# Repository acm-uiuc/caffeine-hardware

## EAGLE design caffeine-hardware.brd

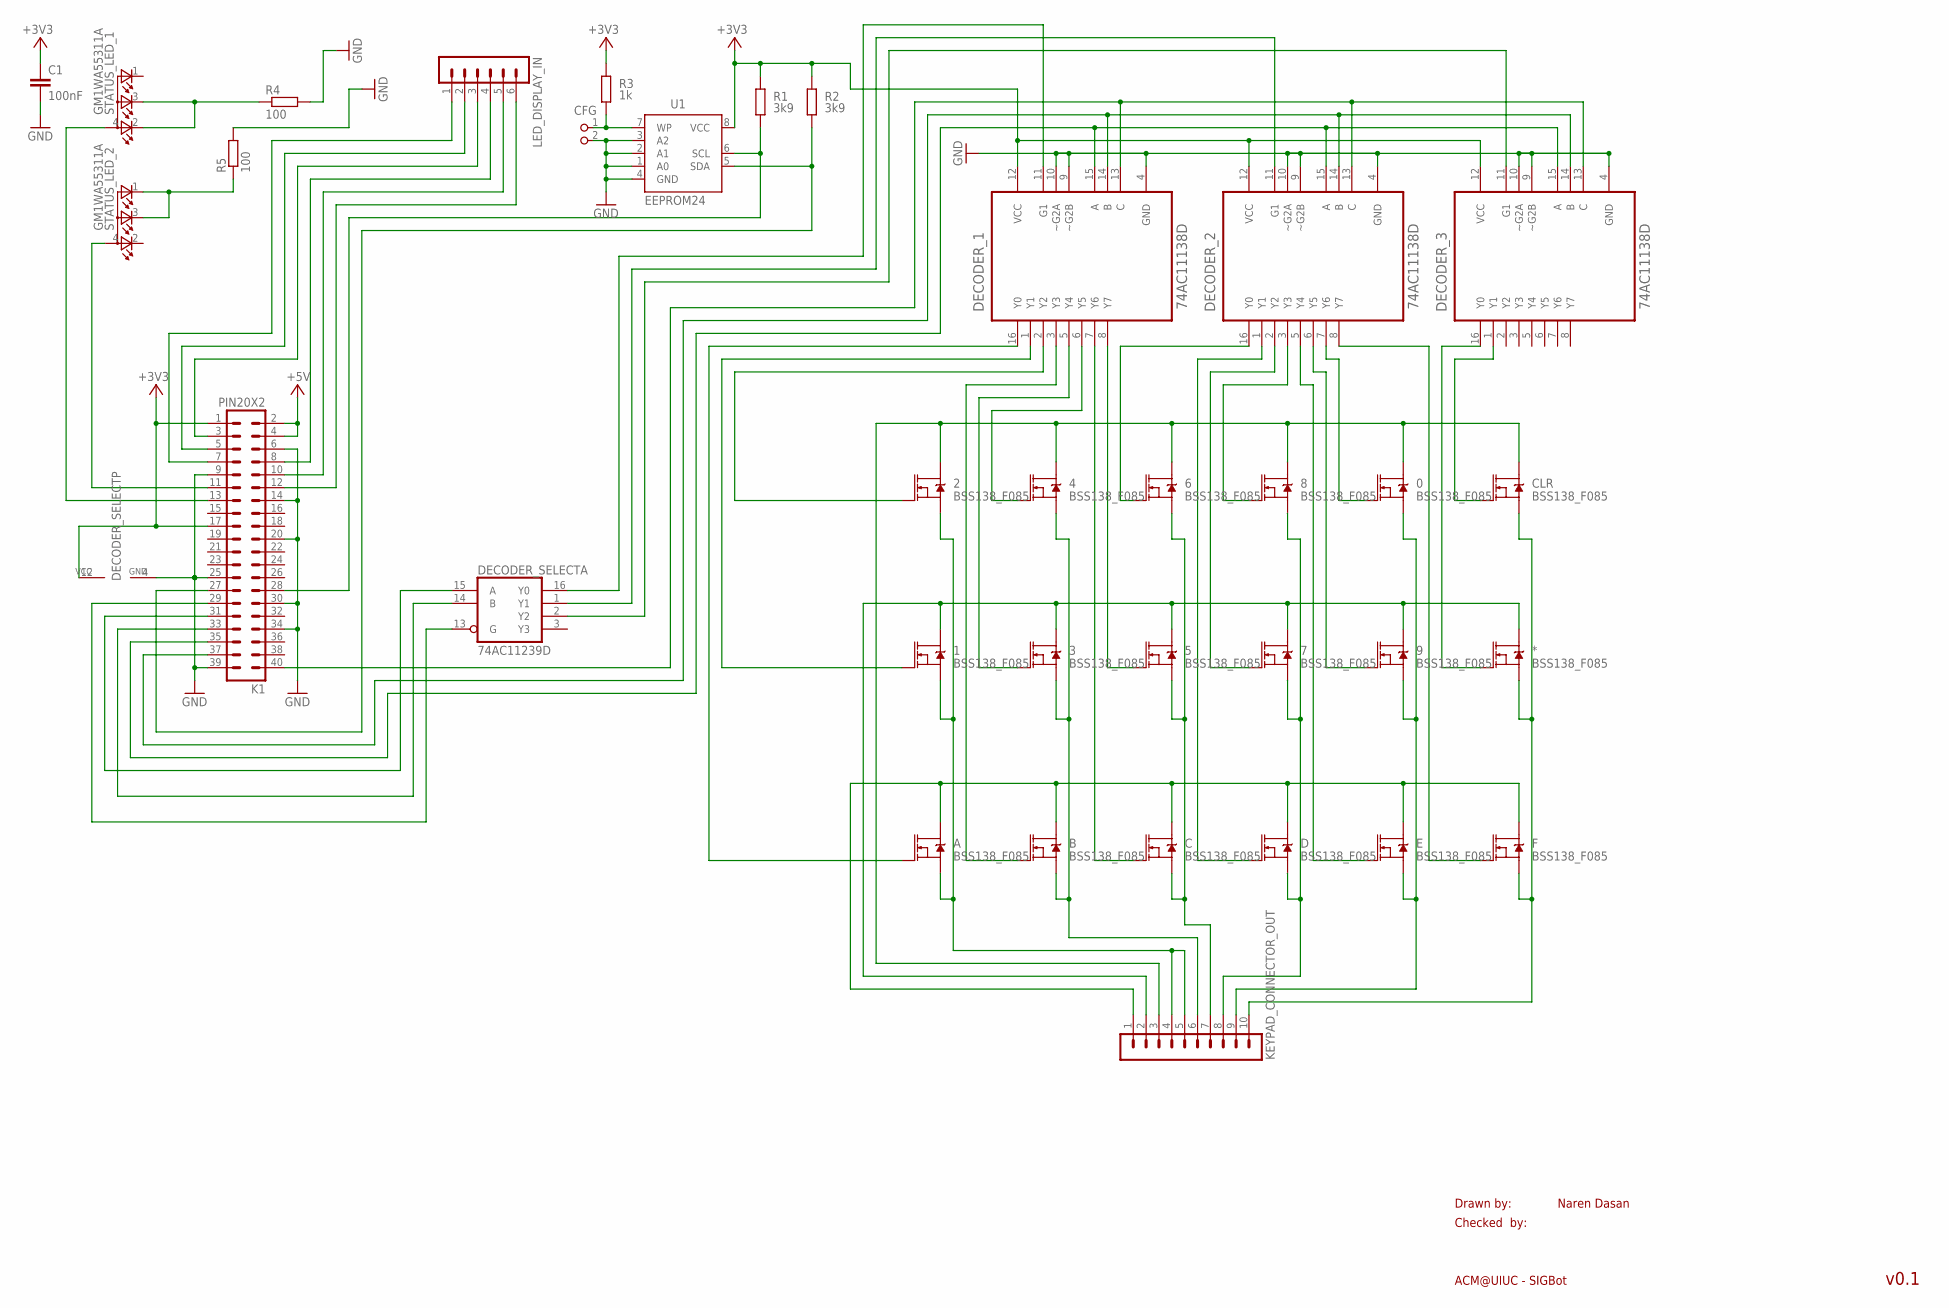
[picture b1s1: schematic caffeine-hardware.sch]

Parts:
0, 1, 2, 3, 4, 5, 6, 7, 8, 9: BSS138_F085; SOT23-3
*: BSS138_F085; SOT23-3
A: BSS138_F085; SOT23-3
B: BSS138_F085; SOT23-3
C: BSS138_F085; SOT23-3
C1: 100nF; C0805K
CFG: PIN2_100; PIN_W_2
CLR: BSS138_F085; SOT23-3
D: BSS138_F085; SOT23-3
DECODER_1, DECODER_2, DECODER_3: 74AC11138D; SOIC127P600X175-16N
DECODER_SELECT: 74AC11239D; SO16
E: BSS138_F085; SOT23-3
F: BSS138_F085; SOT23-3
K1: PIN20X2; PIN_20X2
KEYPAD_CONNECTOR_OUT: MA10-1
LED_DISPLAY_IN: MA06-1
R1, R2: 3k9; M0805; TOLERANCE 5%
R3: 1k; M0805; TOLERANCE 5%
R4, R5: 100; R0805
STATUS_LED_1, STATUS_LED_2: GM1WA55311A
U1: EEPROM24; SOIC8

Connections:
+3V3: C1.1, DECODER_1.12 (VCC), DECODER_2.12 (VCC), DECODER_3.12 (VCC), DECODER_SELECT.12 (VCC), K1.1, K1.17, R1.2, R2.2, R3.2, U1.8 (VCC)
+5V: K1.2, K1.4
GND: C1.2, CFG.2, DECODER_1.4 (GND), DECODER_1.9 (~G2B), DECODER_1.10 (~G2A), DECODER_2.4 (GND), DECODER_2.9 (~G2B), DECODER_2.10 (~G2A), DECODER_3.4 (GND), DECODER_3.9 (~G2B), DECODER_3.10 (~G2A), DECODER_SELECT.4 (GND), K1.6, K1.9, K1.14, K1.20, K1.25, K1.30, K1.34, K1.39, R4.2, R5.2, U1.1 (A0), U1.2 (A1), U1.3 (A2), U1.4 (GND)
unnamed: K1.28, R1.1, U1.6 (SCL)
unnamed: K1.27, R2.1, U1.5 (SDA)
unnamed: CFG.1, R3.1, U1.7 (WP)
unnamed: A.3 (D), B.3 (D), C.3 (D), D.3 (D), E.3 (D), F.3 (D), KEYPAD_CONNECTOR_OUT.1
unnamed: 1.3 (D), 3.3 (D), 5.3 (D), 7.3 (D), 9.3 (D), *.3 (D), KEYPAD_CONNECTOR_OUT.2
unnamed: 0.3 (D), 2.3 (D), 4.3 (D), 6.3 (D), 8.3 (D), CLR.3 (D), KEYPAD_CONNECTOR_OUT.3
unnamed: 5.2 (S), 6.2 (S), C.2 (S), KEYPAD_CONNECTOR_OUT.7
unnamed: 7.2 (S), 8.2 (S), D.2 (S), KEYPAD_CONNECTOR_OUT.8
unnamed: 1.2 (S), 2.2 (S), A.2 (S), KEYPAD_CONNECTOR_OUT.4, KEYPAD_CONNECTOR_OUT.5
unnamed: DECODER_1.11 (G1), DECODER_SELECT.16 (Y0)
unnamed: 0.2 (S), 9.2 (S), E.2 (S), KEYPAD_CONNECTOR_OUT.9
unnamed: *.2 (S), CLR.2 (S), F.2 (S), KEYPAD_CONNECTOR_OUT.10
unnamed: 3.2 (S), 4.2 (S), B.2 (S), KEYPAD_CONNECTOR_OUT.6
unnamed: DECODER_SELECT.14 (B), K1.33
unnamed: DECODER_1.15 (A), DECODER_2.15 (A), DECODER_3.15 (A), K1.35
unnamed: DECODER_1.14 (B), DECODER_2.14 (B), DECODER_3.14 (B), K1.37
unnamed: DECODER_1.13 (C), DECODER_2.13 (C), DECODER_3.13 (C), K1.40
unnamed: DECODER_SELECT.15 (A), K1.31
unnamed: DECODER_2.11 (G1), DECODER_SELECT.1 (Y1)
unnamed: DECODER_3.11 (G1), DECODER_SELECT.2 (Y2)
unnamed: DECODER_SELECT.13 (G), K1.29
unnamed: A.1 (G), DECODER_1.16 (Y0)
unnamed: 1.1 (G), DECODER_1.1 (Y1)
unnamed: 2.1 (G), DECODER_1.2 (Y2)
unnamed: B.1 (G), DECODER_1.3 (Y3)
unnamed: 3.1 (G), DECODER_1.5 (Y4)
unnamed: 4.1 (G), DECODER_1.6 (Y5)
unnamed: C.1 (G), DECODER_1.7 (Y6)
unnamed: 5.1 (G), DECODER_1.8 (Y7)
unnamed: K1.7, LED_DISPLAY_IN.1
unnamed: K1.5, LED_DISPLAY_IN.2
unnamed: K1.8, LED_DISPLAY_IN.4
unnamed: K1.3, LED_DISPLAY_IN.3
unnamed: K1.12, LED_DISPLAY_IN.6
unnamed: K1.10, LED_DISPLAY_IN.5
unnamed: K1.11, STATUS_LED_2.4 (A)
unnamed: K1.13, STATUS_LED_1.4 (A)
unnamed: R4.1, STATUS_LED_1.2 (CRED), STATUS_LED_1.3 (CBLUE)
unnamed: R5.1, STATUS_LED_2.1 (CGREEN), STATUS_LED_2.3 (CBLUE)
unnamed: 6.1 (G), DECODER_2.16 (Y0)
unnamed: D.1 (G), DECODER_2.1 (Y1)
unnamed: 7.1 (G), DECODER_2.2 (Y2)
unnamed: 8.1 (G), DECODER_2.3 (Y3)
unnamed: DECODER_2.5 (Y4), E.1 (G)
unnamed: 9.1 (G), DECODER_2.6 (Y5)
unnamed: 0.1 (G), DECODER_2.7 (Y6)
unnamed: DECODER_2.8 (Y7), F.1 (G)
unnamed: *.1 (G), DECODER_3.16 (Y0)
unnamed: CLR.1 (G), DECODER_3.1 (Y1)

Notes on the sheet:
Drawn by:
Checked by:
ACM@UIUC - SIGBot
Naren Dasan
v0.1

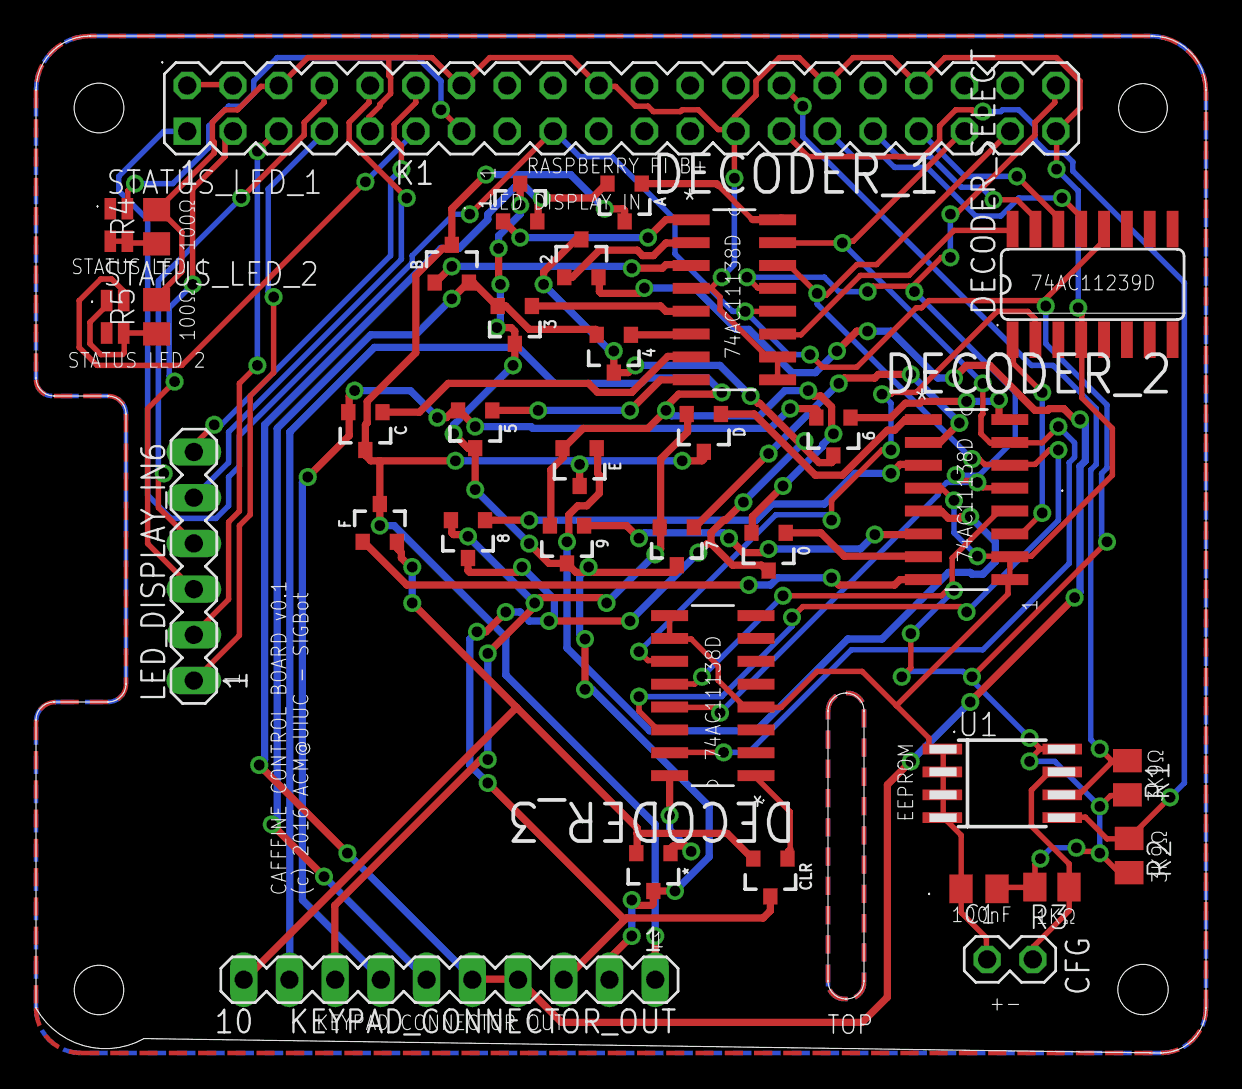
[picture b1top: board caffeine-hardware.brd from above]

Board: 2 copper layers, 65.0 x 56.5 mm, 35 parts (0 on the bottom side), 52 nets.

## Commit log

2016-12-19 silkscreen
2016-12-19 pin marker
2016-12-20 using decoders
2016-12-21 using n channel

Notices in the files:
caffeine-hardware.brd:
(c) 2016 ACM@UIUC - SIGBot
parts and their libraries:
SparkFun-DiscreteSemi: Licensing: Creative Commons ShareAlike 4.0 International - https://creativecommons.org/licenses/by-sa/4.0
